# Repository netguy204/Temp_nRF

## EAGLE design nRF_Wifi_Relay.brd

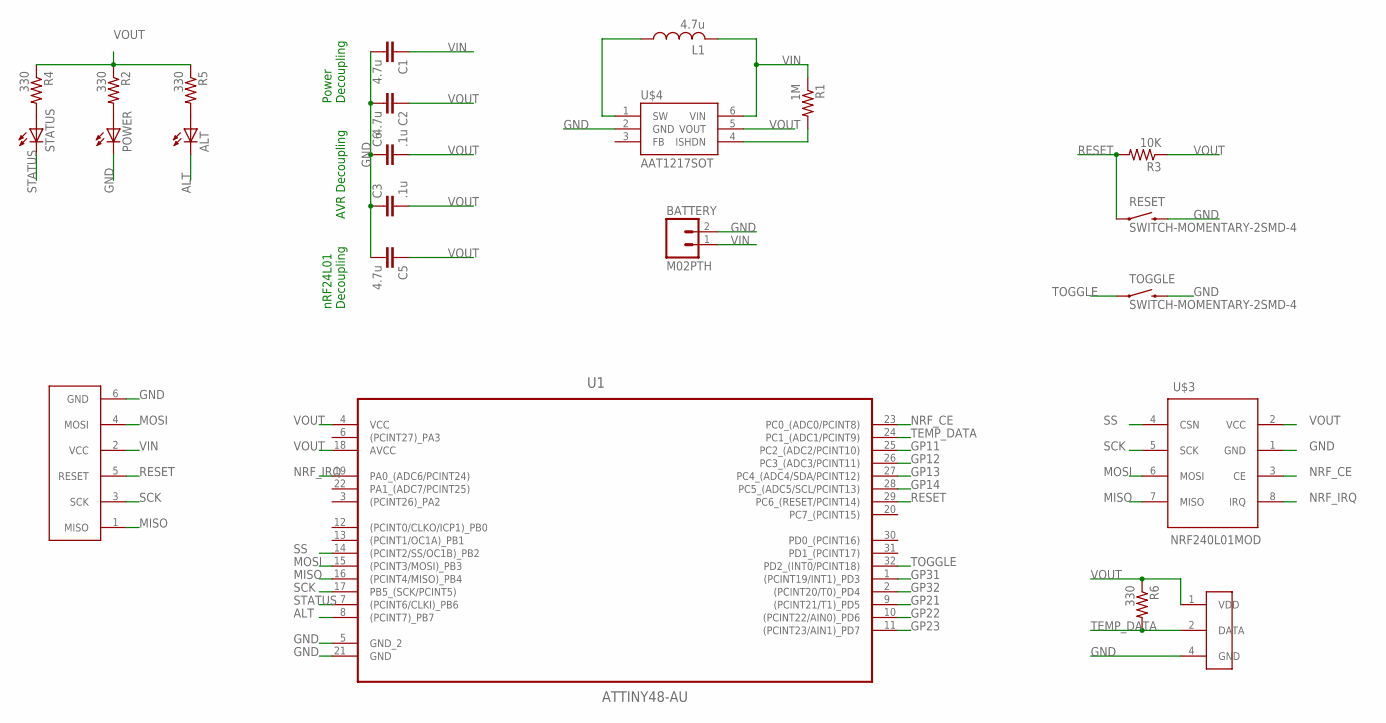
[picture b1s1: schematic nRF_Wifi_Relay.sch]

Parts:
ALT: LEDCHIPLED_0603; CHIPLED_0603
BATTERY: M02PTH; 1X02
C1, C2, C5: 4.7u; C0805
C3, C6: .1u; C0603
L1: 4.7u; L2825P
POWER: LEDCHIPLED_0603; CHIPLED_0603
R1: 1M; R0805
R2, R4, R5, R6: 330; R0805
R3: 10K; R0603
RESET: SWITCH-MOMENTARY-2SMD-4; TACTILE_SWITCH_TALL
STATUS: LEDCHIPLED_0603; CHIPLED_0603
TOGGLE: SWITCH-MOMENTARY-2SMD-4; TACTILE_SWITCH_TALL
U1: ATTINY48-AU; QFP80P900X900X120-32N
U$1: ISP
U$2: DHT11
U$3: NRF240L01MOD
U$4: AAT1217SOT; SOT23-6-RIGHT

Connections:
ALT: ALT.C, U1.8 ((PCINT7)_PB7)
GND: BATTERY.2, C1.2, C2.2, C3.1, C5.2, C6.1, POWER.C, RESET.B2 (2), TOGGLE.B2 (2), U1.5 (GND_2), U1.21 (GND), U$1.6 (GND), U$2.4 (GND), U$3.1 (GND), U$4.2 (GND)
GP11: U1.25 (PC2_(ADC2/PCINT10))
GP12: U1.26 (PC3_(ADC3/PCINT11))
GP13: U1.27 (PC4_(ADC4/SDA/PCINT12))
GP14: U1.28 (PC5_(ADC5/SCL/PCINT13))
GP21: U1.9 ((PCINT21/T1)_PD5)
GP22: U1.10 ((PCINT22/AIN0)_PD6)
GP23: U1.11 ((PCINT23/AIN1)_PD7)
GP31: U1.1 ((PCINT19/INT1)_PD3)
GP32: U1.2 ((PCINT20/T0)_PD4)
MISO: U1.16 ((PCINT4/MISO)_PB4), U$1.1 (MISO), U$3.7 (MISO)
MOSI: U1.15 ((PCINT3/MOSI)_PB3), U$1.4 (MOSI), U$3.6 (MOSI)
unnamed: R4.2, STATUS.A
unnamed: POWER.A, R2.2
unnamed: ALT.A, R5.2
unnamed: L1.1, U$4.1 (SW)
unnamed: R1.2, U$4.4 (ISHDN)
NRF_CE: U1.23 (PC0_(ADC0/PCINT8)), U$3.3 (CE)
NRF_IRQ: U1.19 (PA0_(ADC6/PCINT24)), U$3.8 (IRQ)
RESET: R3.2, RESET.A2 (1), U1.29 (PC6_(RESET/PCINT14)), U$1.5 (RESET)
SCK: U1.17 (PB5_(SCK/PCINT5)), U$1.3 (SCK), U$3.5 (SCK)
SS: U1.14 ((PCINT2/SS/OC1B)_PB2), U$3.4 (CSN)
STATUS: STATUS.C, U1.7 ((PCINT6/CLKI)_PB6)
TEMP_DATA: R6.2, U1.24 (PC1_(ADC1/PCINT9)), U$2.2 (DATA)
TOGGLE: TOGGLE.A2 (1), U1.32 (PD2_(INT0/PCINT18))
VIN: BATTERY.1, C1.1, L1.2, R1.1, U$1.2 (VCC), U$4.6 (VIN)
VOUT: C2.1, C3.2, C5.1, C6.2, R2.1, R3.1, R4.1, R5.1, R6.1, U1.4 (VCC), U1.18 (AVCC), U$2.1 (VDD), U$3.2 (VCC), U$4.5 (VOUT)

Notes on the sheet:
AVR Decoupling
Power Decoupling
nRF24L01 Decoupling

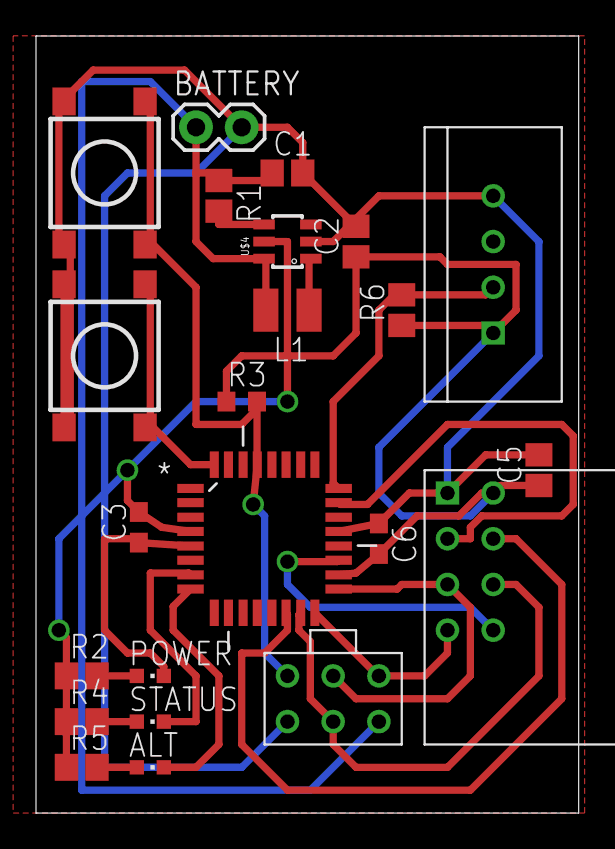
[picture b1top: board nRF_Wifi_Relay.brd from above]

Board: 2 copper layers, 30.1 x 43.2 mm, 23 parts (0 on the bottom side), 19 nets.

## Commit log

2015-02-21 pre assembly version of nRF only temp board
2015-03-24 circuit is looking blinky!

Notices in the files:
parts and their libraries:
SparkFun-Electromechanical: Licensing: Creative Commons ShareAlike 4.0 International - https://creativecommons.org/licenses/by-sa/4.0
